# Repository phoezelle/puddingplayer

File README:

penser à :
passer en azerty + partage ram + …
  raspi-config
ctreate root passwd and log root
  sudo passwd root
update and upgrade apt-get
  apt-get clean
  apt-get update
  apt-get upgrade
install screen
  apt-get screen
install openframworks + script : dependancies.sh + scripts : codecs.sh
  cd /home/pi
  wget http://openframeworks.cc/versions/v0.9.3/of_v0.9.3_linuxarmv6l_release.tar.gz
  mkdir openFrameworks
  tar vxfz of_v0.9.3_linuxarmv6l_release.tar.gz -C openFrameworks --strip-components 1
  cd /home/pi/openFrameworks/scripts/linux/debian
  ./install_dependencies.sh
  ./install_codecs.sh
install wiringpi
  apt-get install wiringPi
install RF24
  $ mkdir nrf24l01
  $ cd nrf24l01
  $ git clone https://github.com/TMRh20/RF24.git
  $ cd RF24
  $ make
  $ sudo make install
compil openframeworks
  make Release -j4 -C /home/pi/openFrameworks/libs/openFrameworksCompiled/project
add my ssh key
  (on my terminal) ssh-copy-id pi@X.X.X.X (IP of pi)
install git-core and clone git repo
  apt-get install git-core
  cd /home/pi/openFrameworks/apps/myApps/
  git clone https://github.com/phoezelle/puddingplayer.git puddingplayer
compil project
  cd puddingplayer/
  make -j4
test it in screen attach mode
  screen -S pudding -m  /home/pi/openFrameworks/apps/myApps/puddingplayer/bin/puddingplayer
create init script
  nano /etc/init.d/puddingplayer
  chmod +x /etc/init.d/puddingplayer
create call script
  nano /etc/init.d/composecall
  chmod +x /etc/init.d/composecall
add call to the script in rc.local
  nano /etc/rc.local
hdmi auto hot plug
  nano /boot/config.txt
définir un réseau de secours
    nano /etc/wpa_supplicant/wpa_supplicant.conf
disable screen saver
    nano /etc/kbd/config
permit root login
    sudo nano /etc/ssh/sshd_config
active spi (dtparam=spi=on)
    sudo nano /boot/config.txt

passer en lecture seule le pi
  http://blog.pi3g.com/2014/04/make-raspbian-system-read-only/

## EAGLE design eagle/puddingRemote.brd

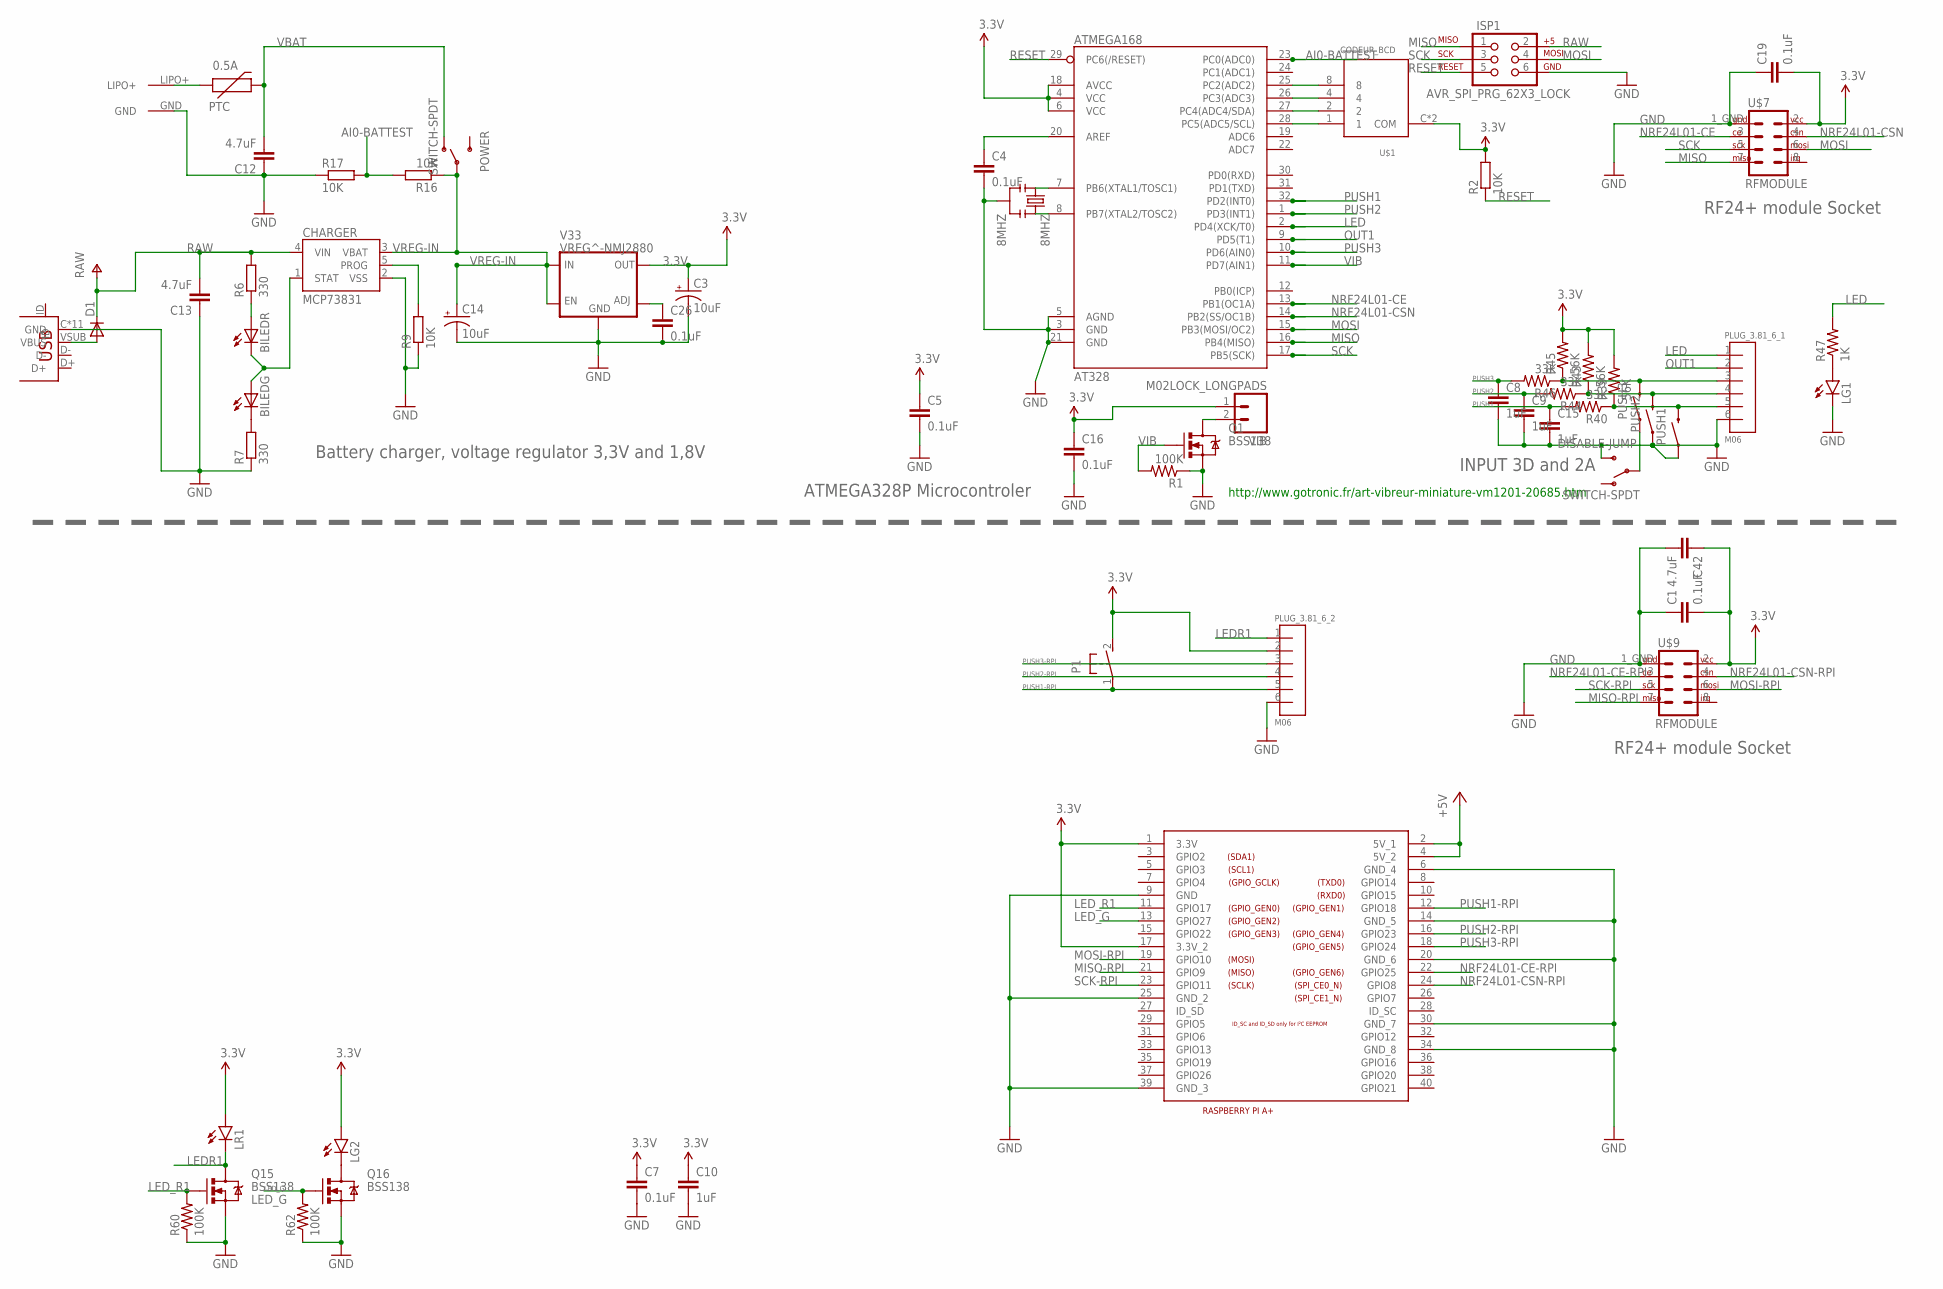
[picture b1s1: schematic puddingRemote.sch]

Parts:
0.5A: PTC; PTC-1210
8MHZ: 8MHZ; RESONATOR-SMD
AT328: ATMEGA168; TQFP32-08
BILED: BILED; 2XLED
C1, C4, C5, C7, C16, C19, C26: 0.1uF; C0603
C3, C14: 10uF; EIA3216
C8, C9, C10, C15: 1uF; C0603
C12, C13, C42: 4.7uF; C0603
CHARGER: MCP73831; SOT23-5
D1: DIODESMA-KIT; SMA-DIODE-KIT
DISABLE-JUMP: SWITCH-SPDT; SWITCH-102011SAQN
ISP1: AVR_SPI_PRG_62X3_LOCK; 2X3_LOCK
LG1, LG2: LED1206; LED-1206
LR1: LED1206; LED-1206
P1: 31-XX; B3F-31XX
PLUG_3.81_6_1, PLUG_3.81_6_2: M06; PLUG_06
POWER: SWITCH-SPDT; SWITCH-102011SAQN
PUSH1, PUSH2, PUSH3: SWITCH-MOMENTARY-2PTH; TACTILE-PTH
Q1, Q15, Q16: BSS138; SOT23-3
R1, R60, R62: 100K; 0603-RES
R2, R9, R16, R17: 10K; R0603
R6, R7: 330; R0603
R39, R43, R45: 56K; 0603-RES
R40, R44, R46: 33K; 0603-RES
R47: 1K; 0603-RES
U$1: CODEUR_BCD; MCRM4HAF-10R-V-B
U$2: USB-MICROB; USB-MICROB-10103594-0001LF
U$4: RASPIRASPIB; RASPIB
U$7, U$9: RFMODULE; 2X5_RFMODULE
U$8: LIPO_PAD; 2X1_LIPO_PAD
V33: VREG^-NMJ2880; SOT-89
VIB: M02LOCK_LONGPADS; 1X02_LOCK_LONGPADS

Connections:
1: AT328.28 (PC5(ADC5/SCL)), U$1.1
2: AT328.27 (PC4(ADC4/SDA)), U$1.2
3.3V: AT328.4 (VCC), AT328.6 (VCC), AT328.18 (AVCC), C1.2, C3.A (+), C5.1, C7.1, C10.1, C16.1, C19.2, C42.1, LG2.A, LR1.A, P1.2 (S), PLUG_3.81_6_2.2, R2.2, R39.2, R43.2, R45.2, U$1.C (COM), U$1.C2 (COM), U$4.1 (3.3V), U$4.17 (3.3V_2), U$7.2 (VCC), U$9.2 (VCC), V33.4 (OUT), VIB.1
4: AT328.26 (PC3(ADC3)), U$1.4
8: AT328.25 (PC2(ADC2)), U$1.8
+5V: U$4.2 (5V_1), U$4.4 (5V_2)
AI0-BATTEST: AT328.23 (PC0(ADC0)), R16.2, R17.2
AREF: AT328.20 (AREF), C4.1
GND: 8MHZ.2, AT328.3 (GND), AT328.5 (AGND), AT328.21 (GND), C1.1, C3.C (-), C4.2, C5.2, C7.2, C8.2, C9.2, C10.2, C12.1, C13.1, C14.C (-), C15.2, C16.2, C19.1, C26.2, C42.2, CHARGER.2 (VSS), DISABLE-JUMP.3 (S), ISP1.6, LG1.C, PLUG_3.81_6_1.6, PLUG_3.81_6_2.6, PUSH1.1, PUSH2.1, Q1.2 (S), Q15.2 (S), Q16.2 (S), R1.1, R7.1, R9.1, R17.1, R60.1, R62.1, U$2.C (GND), U$2.C1 (GND), U$2.C3 (GND), U$2.C4 (GND), U$2.C5 (GND), U$2.C6 (GND), U$2.GND, U$2.P$1 (GND), U$2.P$2 (GND), U$2.P$3 (GND), U$2.P$4 (GND), U$4.6 (GND_4), U$4.9 (GND), U$4.14 (GND_5), U$4.20 (GND_6), U$4.25 (GND_2), U$4.30 (GND_7), U$4.34 (GND_8), U$4.39 (GND_3), U$7.1_GND (GND), U$8.GND, U$9.1_GND (GND), V33.2 (GND)
LED: AT328.2 (PD4(XCK/T0)), PLUG_3.81_6_1.1, R47.2
LEDR1: LR1.C, PLUG_3.81_6_2.1, Q15.3 (D)
LED_G: Q16.1 (G), R62.2, U$4.13 (GPIO27)
LED_R1: Q15.1 (G), R60.2, U$4.11 (GPIO17)
LG1: LG2.C, Q16.3 (D)
MISO: AT328.16 (PB4(MISO)), ISP1.1, U$7.7 (MISO)
MISO-RPI: U$4.21 (GPIO9), U$9.7 (MISO)
MOSI: AT328.15 (PB3(MOSI/OC2)), ISP1.4, U$7.6 (MOSI)
MOSI-RPI: U$4.19 (GPIO10), U$9.6 (MOSI)
unnamed: C26.1, V33.3 (ADJ)
unnamed: D1.A, U$2.VSUB (VBUS)
unnamed: Q1.3 (D), VIB.2
unnamed: 8MHZ.1, AT328.7 (PB6(XTAL1/TOSC1))
unnamed: 8MHZ.3, AT328.8 (PB7(XTAL2/TOSC2))
unnamed: LG1.A, R47.1
unnamed: DISABLE-JUMP.C, PUSH3.1
unnamed: BILED.A2 (A), R6.1
unnamed: BILED.C3 (C), R7.2
unnamed: CHARGER.5 (PROG), R9.2
NRF24L01-CE: AT328.13 (PB1(OC1A)), U$7.3 (CE)
NRF24L01-CE-RPI: U$4.22 (GPIO25), U$9.3 (CE)
NRF24L01-CSN: AT328.14 (PB2(SS/OC1B)), U$7.4 (CSN)
NRF24L01-CSN-RPI: U$4.24 (GPIO8), U$9.4 (CSN)
OUT1: AT328.9 (PD5(T1)), PLUG_3.81_6_1.2
PUSH1: AT328.32 (PD2(INT0)), C15.1, R40.2
PUSH1-RPI: P1.1, PLUG_3.81_6_2.5, U$4.12 (GPIO18)
PUSH2: AT328.1 (PD3(INT1)), C9.1, R44.2
PUSH2-RPI: PLUG_3.81_6_2.4, U$4.16 (GPIO23)
PUSH3: AT328.10 (PD6(AIN0)), C8.1, R46.2
PUSH3-RPI: PLUG_3.81_6_2.3, U$4.18 (GPIO24)
RAW: C13.2, CHARGER.4 (VIN), D1.C, ISP1.2, R6.2
RESET: AT328.29 (PC6(/RESET)), ISP1.5, R2.1
S1: PLUG_3.81_6_1.5, PUSH1.3 (2), R39.1, R40.1
S2: PLUG_3.81_6_1.4, PUSH2.3 (2), R43.1, R44.1
S3: PLUG_3.81_6_1.3, PUSH3.3 (2), R45.1, R46.1
SCK: AT328.17 (PB5(SCK)), ISP1.3, U$7.5 (SCK)
SCK-RPI: U$4.23 (GPIO11), U$9.5 (SCK)
STAT: BILED.A1 (A), BILED.C4 (C), CHARGER.1 (STAT)
VBAT: 0.5A.2, C12.2, POWER.1 (O)
VBAT-RAW: 0.5A.1, U$8.LIPO+
VIB: AT328.11 (PD7(AIN1)), Q1.1 (G), R1.2
VREG-IN: C14.A (+), CHARGER.3 (VBAT), POWER.C, R16.1, V33.1 (EN), V33.5 (IN)

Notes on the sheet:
RF24+ module Socket
Battery charger, voltage regulator 3,3V and 1,8V
INPUT 3D and 2A
http://www.gotronic.fr/art-vibreur-miniature-vm1201-20685.htm
ATMEGA328P Microcontroler

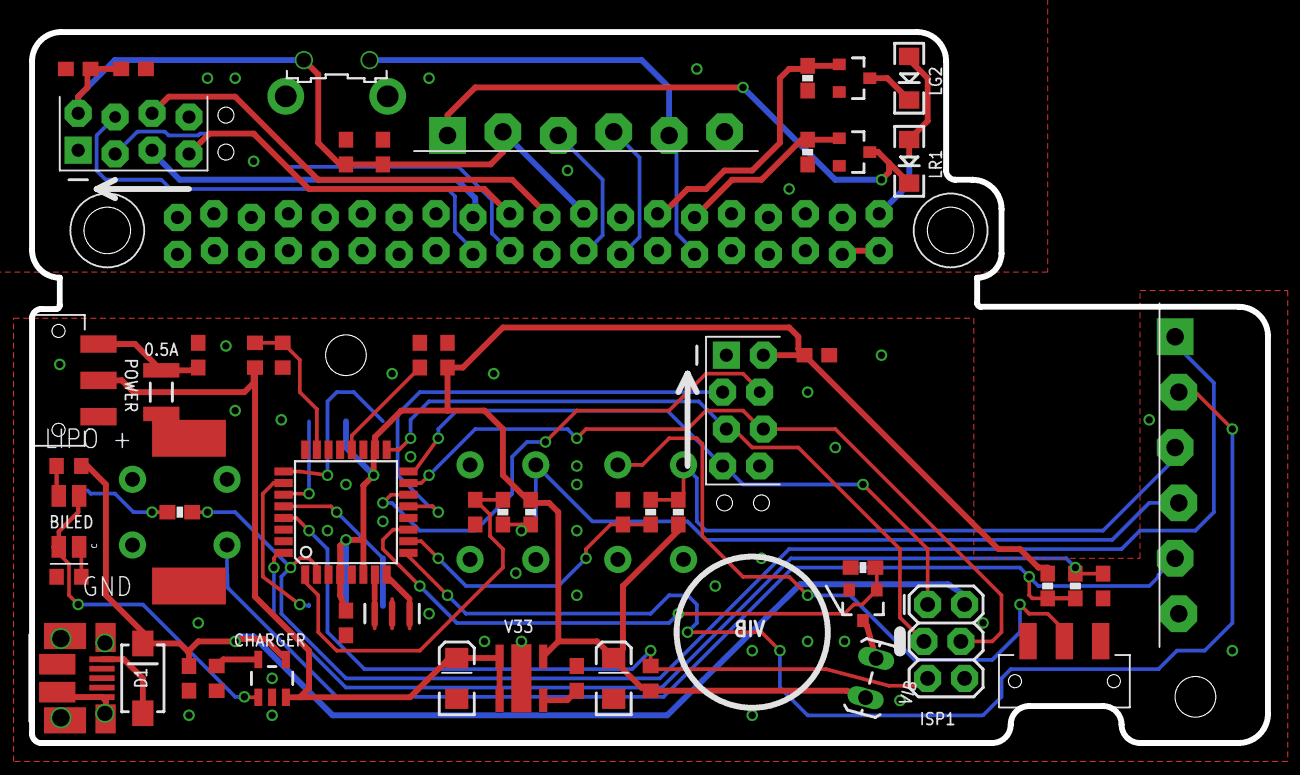
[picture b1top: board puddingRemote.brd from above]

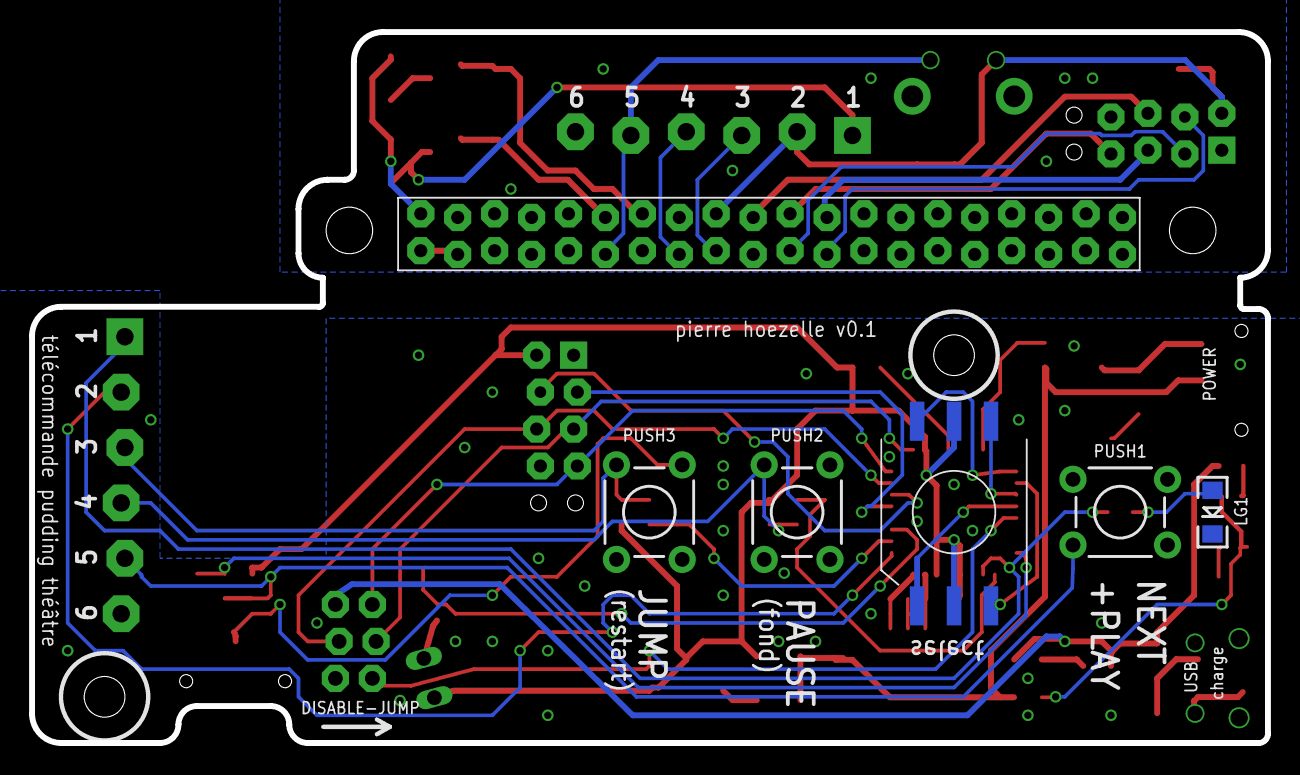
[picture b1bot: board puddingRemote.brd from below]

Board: 2 copper layers, 85.0 x 48.9 mm, 61 parts (6 on the bottom side), 51 nets.

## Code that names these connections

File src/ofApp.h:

#pragma once

#include "ofMain.h"
#include "checkremote.h"


class ofApp : public ofBaseApp{
  
public:
  
  Checkremote thread;
  
  void setup();
  void update();
  void draw();
  void exit();
  
  void keyPressed(int key);
  void keyReleased(int key);
  void mouseMoved(int x, int y );
  void mouseDragged(int x, int y, int button);
  void mousePressed(int x, int y, int button);
  void mouseReleased(int x, int y, int button);
  void mouseEntered(int x, int y);
  void mouseExited(int x, int y);
  void windowResized(int w, int h);
  void dragEvent(ofDragInfo dragInfo);
  void gotMessage(ofMessage msg);
  
  //SETUP AND PREF
  void definePlateform();
  void usbstickMount();
  void buildMediaList();
  void getPref();
  void checkNetwork();
  void setcurrentCharacter(int _character);
  
  bool pi,firstlaunch;
  int posX,posY,width,height,loglevel;
  string firstMessage;
  vector <string> characterList;
  vector <vector <string>> mediaList;
  vector <string> backgroundList;
  
  //GPIO
  void initGPIO();
  void checkGPIO();
  void getAnalogBattery();
  
  void checkREMOTE();
  
  int ledG_value;
  int ledG_state;
  uint64_t ledG_time_on;
  uint64_t ledG_time_period;
  
  int ledR_state;
  int ledR_value;
  uint64_t ledR_time_on;
  uint64_t ledR_time_period;
  //ofThreadChannel<int> myThreadChannel;
  void checkLed();
  void flash_ledG(int f);
  void flash_ledR(int f);
  

#define PIN_NUM 3
#define PUSH1 1
#define PUSH2 4
#define PUSH3 5

#define LEDR 0
#define LEDG 2
  
  
  int laststate[PIN_NUM];
  int pin[PIN_NUM];
  uint64_t startpushtime[PIN_NUM];
  bool longpush[PIN_NUM];
  

  
  //VIDEOPLAYER
  ofVideoPlayer 		*fingerMovie;
  ofVideoPlayer     *fingerMovie2;
  int nvideo;
  int gochangevideo;
  bool isplayground;
  void play();
  void playNext();
  void pausePlay();
  void playBackground();
  void changeBackground();
  void nextScene();
  void restartScene();
  void clearVideo(int n);
  
  int maxScene, currentScene, currentVideo, currentBackground, currentCharacter,nbMedia;
  string rootDirectory,mediaDirectory,backgroundDirectory;
  
  //UTILITY
  void log(string log,int level,bool color=false);
  
#define WARNING 0
#define USR 1
#define DEBUG 2
#define RAW 3
  

  
  //void checkinputandplayVideo();
  //void playVideoInPath();
  
  
  
  
  
  
};

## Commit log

2016-09-01 first commit2
2016-09-01 first commit3
2016-09-01 add gpio test + fullscreen video
2016-09-01 good pin number
2016-09-01 test another pin than I2C
2016-09-01 add functionality, gpio working
2016-09-01 cleaner
2016-09-01 errors
2016-09-01 bug again
2016-09-01 try avoid green flaw
2016-09-02 add 3 pin (wiring pi 0 2 3) (bcm 17 27 22) and long push mechanism
2016-09-05 try correct last video bug
2016-09-05 add log
2016-09-05 correct duplicate first video in medialist of new scene
2016-09-05 another little bug : restart at the beginning and do not iterate
2016-09-05 add log screen size
2016-09-05 adjust screen size for video
2016-09-05 add black backround
2016-09-05 adjust screen size
2016-09-05 trick video size
2016-09-05 test screen size
2017-01-12 test gpio out
2017-01-12 test without usb stick
2017-01-13 test spi
2017-01-13 simplified test
2017-01-13 add rf24 to check lib
2017-01-13 add linker
2017-01-13 update link
2017-01-13 include receive n8 remote
2017-01-14 test without in
2017-01-14 finally use two program
2017-01-14 test read con in main program
2017-01-14 add read con
2017-01-14 typo
2017-01-14 small error
2017-01-14 try with loop
2017-01-14 oups
2017-01-14 test if block
2017-01-14 test without log
2017-01-14 re log
2017-01-14 un log
2017-01-14 log 1
2017-01-17 add thread
2017-01-17 add call the thread
2017-01-17 add debounce
2017-01-17 do not use thread channel
2017-01-18 no debounce
2017-01-18 add flash
2017-01-18 flash
2017-01-18 simplified
2017-01-18 invert setup
2017-01-18 real pause ?
2017-01-18 do not stop ?
2017-01-18 restop
2017-01-18 avoid black flash
2017-01-18 fix led
2017-01-18 test with two layer of video
2017-01-18 with background
2017-01-18 try fix
2017-01-18 another
2017-01-18 without delete
2017-01-18 asyncload
2017-01-18 no close
2017-01-19 add reboot
2017-01-19 only one character
2017-01-19 robust
2017-01-19 size
2017-01-19 add eagle + arduino manque sender
2017-03-07 add scipt file for rpi

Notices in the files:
parts and their libraries:
SparkFun-Passives: Licensing: Creative Commons ShareAlike 4.0 International - https://creativecommons.org/licenses/by-sa/4.0
